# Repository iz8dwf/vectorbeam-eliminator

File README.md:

# vectorbeam-eliminator
Digital to analog vector monitor adapter for B&amp;W Vectorbeam/Cinematronics arcade

This board is described and demonstrated in this video:
https://www.youtube.com/watch?v=j_siDBxwS5w

It allows using an "Atari"-compatible arcade analog vector monitor with a CCPU arcade logic board.

It is highly recommended that the circuit initial check is done using an oscilloscope in X-Y mode first,
at least for the offset tuning.

A misbehaving CCPU board can output bad vector data that can damage the vector monitor (and its own digital monitor too)!
Make sure the logic board at least is executing correctly or use an oscilloscope as XY display to stay on the safe side.

USE AT YOUR OWN RISK!

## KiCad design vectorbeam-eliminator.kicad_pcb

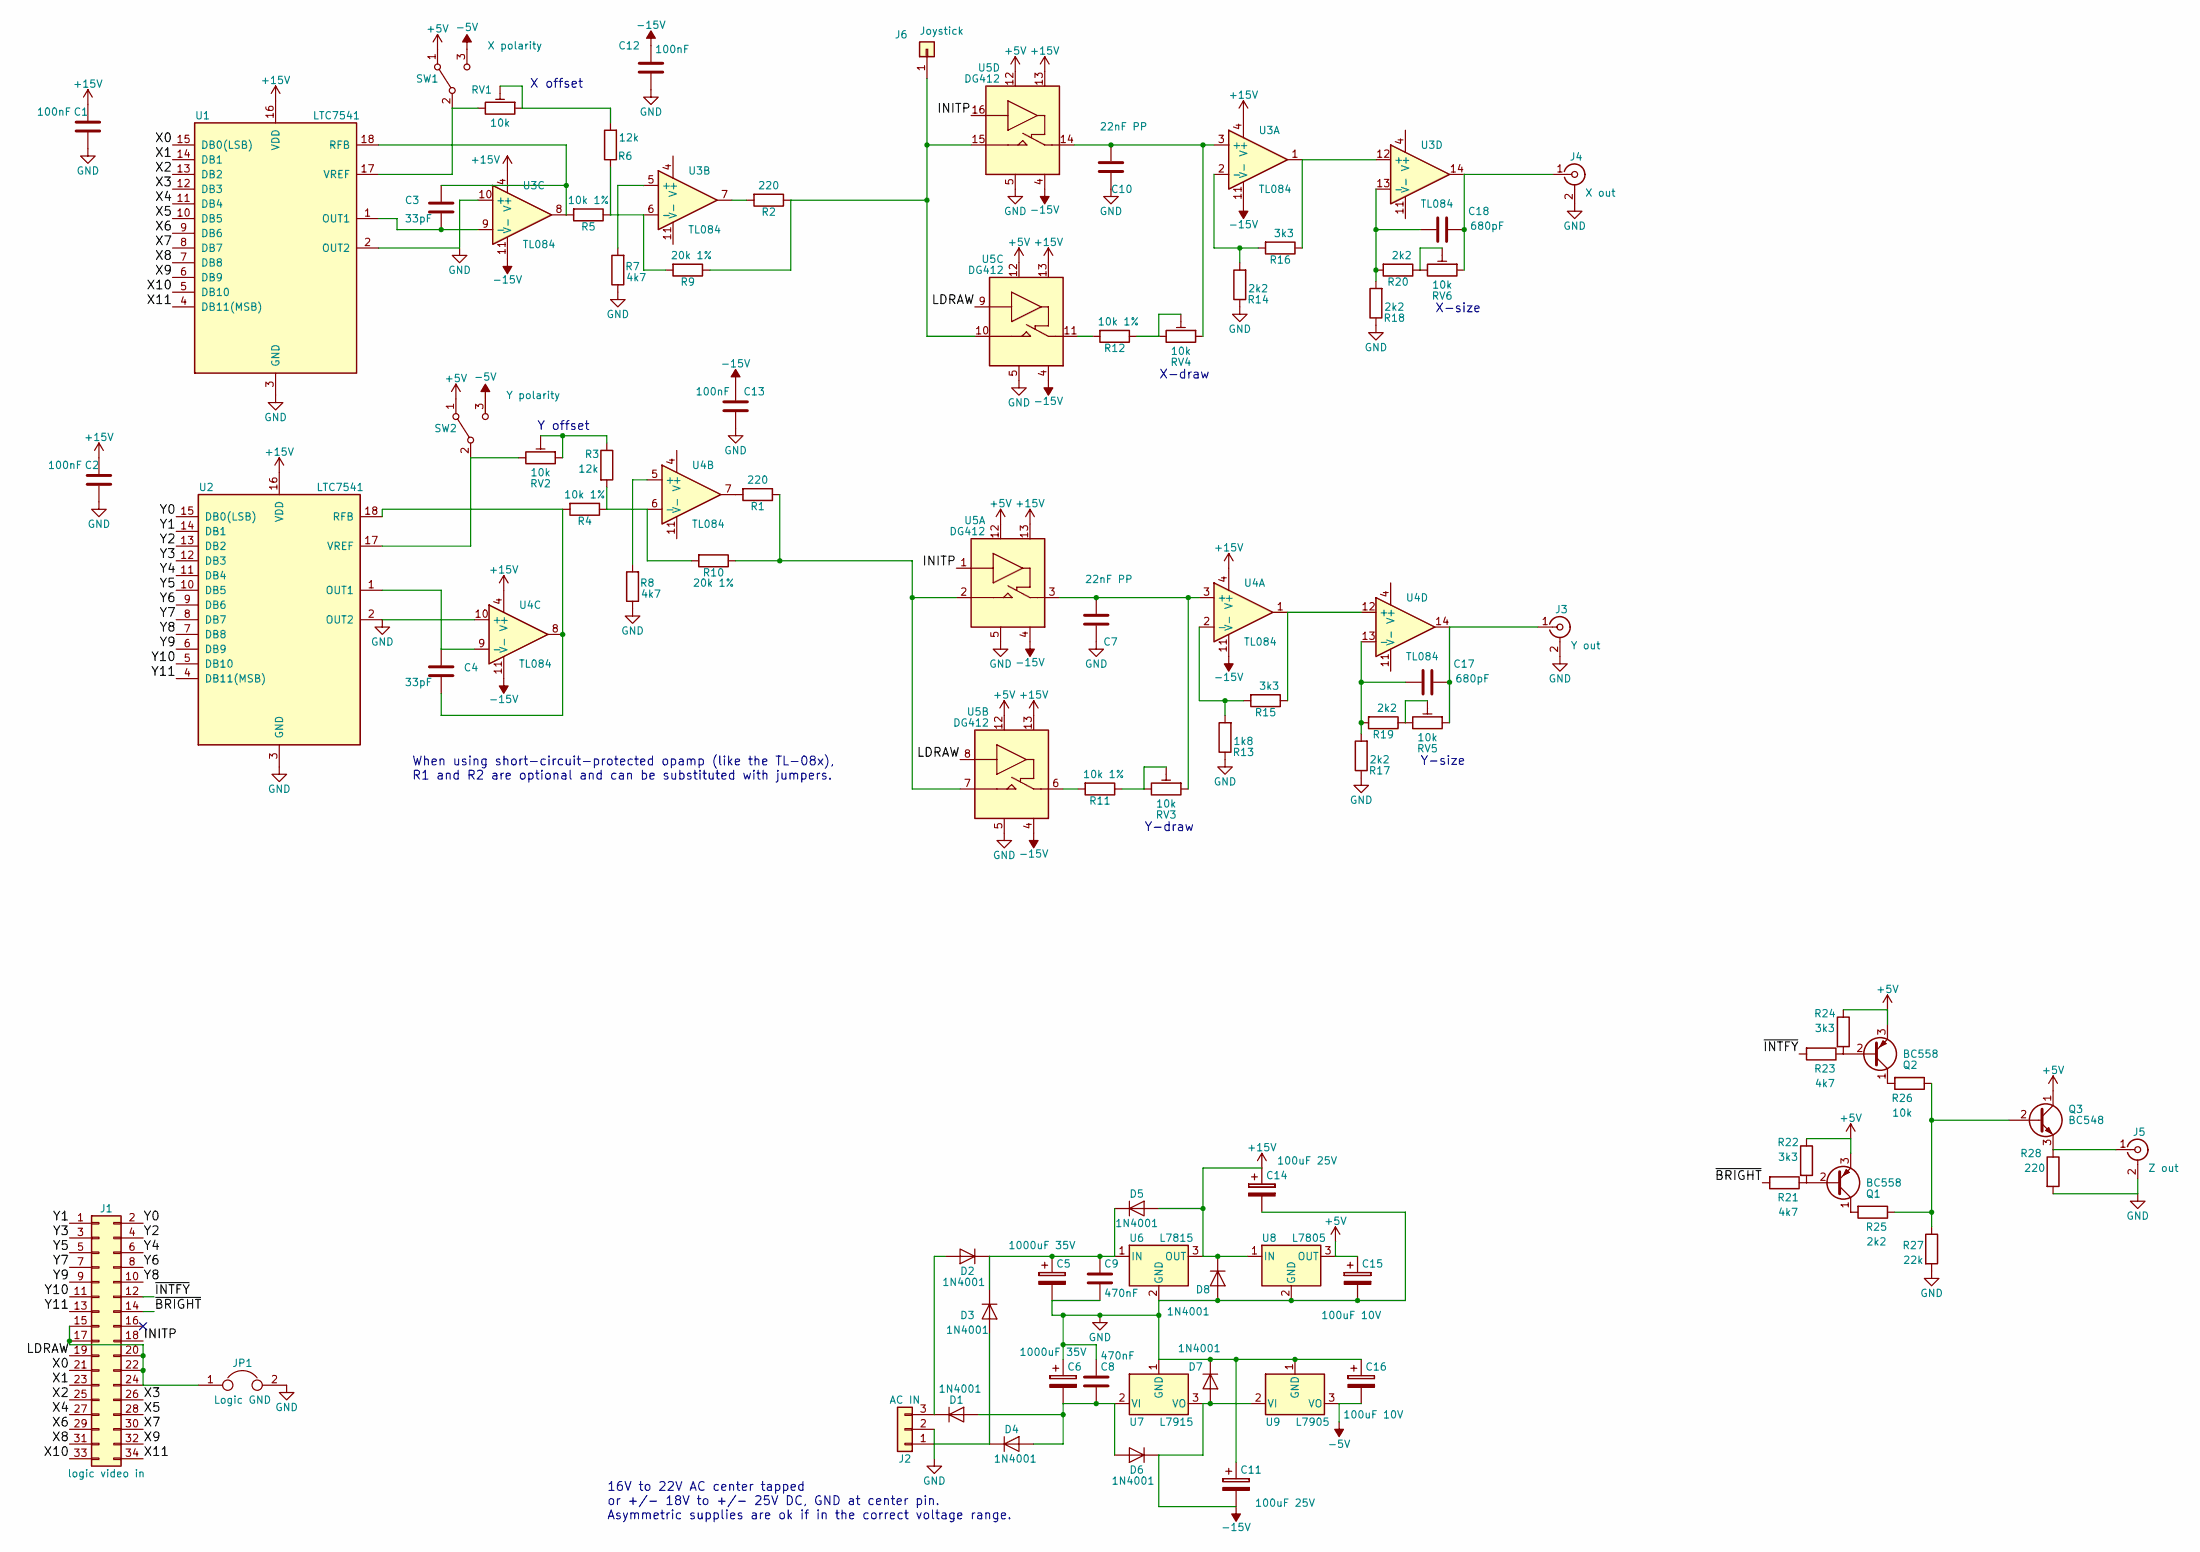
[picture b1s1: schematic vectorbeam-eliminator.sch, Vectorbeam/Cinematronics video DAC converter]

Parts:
C1, C2, C12, C13: 100nF; C_Rect_L7.2mm_W5.5mm_P5.00mm_FKS2_FKP2_MKS2_MKP2
C3, C4: 33pF; C_Disc_D3.8mm_W2.6mm_P2.50mm
C5, C6: 1000uF 35V; CP_Radial_D12.5mm_P5.00mm
C7, C10: 22nF PP; C_Rect_L7.2mm_W7.2mm_P5.00mm_FKS2_FKP2_MKS2_MKP2
C8, C9: 470nF; C_Rect_L7.2mm_W5.5mm_P5.00mm_FKS2_FKP2_MKS2_MKP2
C11, C14: 100uF 25V; CP_Radial_D8.0mm_P2.50mm
C15, C16: 100uF 10V; CP_Radial_D8.0mm_P2.50mm
C17, C18: 680pF; C_Disc_D3.8mm_W2.6mm_P2.50mm
D1, D2, D3, D4, D5, D6, D7, D8: 1N4001; D_DO-41_SOD81_P10.16mm_Horizontal
J1: logic video in; IDC-Header_2x17_Pitch2.54mm_Straight
J2: AC IN; PINHEAD1-3
J3: Y out; phono_single_angled
J4: X out; phono_single_angled
J5: Z out; phono_single_angled
J6: Joystick; Test_Point_Loop_D2.50mm_Drill1.0mm
JP1: Logic GND; PINHEAD1-2
Q1, Q2: BC558; TO-92_Molded_Narrow
Q3: BC548; TO-92_Molded_Narrow
R1, R2, R28: 220; R_1206_HandSoldering
R3, R6: 12k; R_1206_HandSoldering
R4, R5, R11, R12: 10k 1%; R_1206_HandSoldering
R7, R8, R21, R23: 4k7; R_1206_HandSoldering
R9, R10: 20k 1%; R_1206_HandSoldering
R13: 1k8; R_1206_HandSoldering
R14, R17, R18, R19, R20, R25: 2k2; R_1206_HandSoldering
R15, R16, R22, R24: 3k3; R_1206_HandSoldering
R26: 10k; R_1206_HandSoldering
R27: 22k; R_1206_HandSoldering
RV1, RV2, RV3, RV4, RV5, RV6: 10k; Potentiometer_Trimmer_ACP_CA9v_Horizontal_Px10.0mm_Py5.0mm
SW1: X polarity; Pin_Header_Straight_1x03_Pitch2.54mm
SW2: Y polarity; Pin_Header_Straight_1x03_Pitch2.54mm
U1, U2: LTC7541; DIP-18_W7.62mm_Socket
U3, U4: TL084; DIP-14_W7.62mm_Socket
U5: DG412; SOIC-16_3.9x9.9mm_Pitch1.27mm
U6: L7815; TO-220-3_Vertical
U7: L7915; TO-220-3_Vertical
U8: L7805; TO-220-3_Vertical
U9: L7905; TO-220-3_Vertical

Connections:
+5V: C15.1, Q1.3 (E), Q2.3 (E), Q3.1 (C), R22.1, R24.1, SW1.1 (A), SW2.1 (A), U5.12 (VCC), U8.3 (OUT)
+15V: C1.1, C2.1, C14.1, D5.2 (A), D8.1 (K), U1.16 (VDD), U2.16 (VDD), U3.4 (V+), U4.4 (V+), U5.13 (V+), U6.3 (OUT), U8.1 (IN)
-5V: C16.2, SW1.3 (C), SW2.3 (C), U9.3 (VO)
-15V: C11.2, C12.1, C13.1, D6.1 (K), D7.2 (A), U3.11 (V-), U4.11 (V-), U5.4 (V-), U7.3 (VO), U9.2 (VI)
/INITP: J1.18, U5.1 (SW), U5.16 (SW)
/LDRAW: J1.19, U5.8 (SW), U5.9 (SW)
/X0: J1.21, U1.15 (DB0(LSB))
/X1: J1.23, U1.14 (DB1)
/X2: J1.25, U1.13 (DB2)
/X3: J1.26, U1.12 (DB3)
/X4: J1.27, U1.11 (DB4)
/X5: J1.28, U1.10 (DB5)
/X6: J1.29, U1.9 (DB6)
/X7: J1.30, U1.8 (DB7)
/X8: J1.31, U1.7 (DB8)
/X9: J1.32, U1.6 (DB9)
/X10: J1.33, U1.5 (DB10)
/X11: J1.34, U1.4 (DB11(MSB))
/Y0: J1.2, U2.15 (DB0(LSB))
/Y1: J1.1, U2.14 (DB1)
/Y2: J1.4, U2.13 (DB2)
/Y3: J1.3, U2.12 (DB3)
/Y4: J1.6, U2.11 (DB4)
/Y5: J1.5, U2.10 (DB5)
/Y6: J1.8, U2.9 (DB6)
/Y7: J1.7, U2.8 (DB7)
/Y8: J1.10, U2.7 (DB8)
/Y9: J1.9, U2.6 (DB9)
/Y10: J1.11, U2.5 (DB10)
/Y11: J1.13, U2.4 (DB11(MSB))
/~BRIGHT: J1.14, R21.2
/~INTFY: J1.12, R23.2
GND: C1.2, C2.2, C5.2, C6.1, C7.1, C8.1, C9.2, C10.1, C11.1, C12.2, C13.2, C14.2, C15.2, C16.1, D7.1 (K), D8.2 (A), J2.2, J3.2 (Ext), J4.2 (Ext), J5.2 (Ext), JP1.2, R7.1, R8.1, R13.1, R14.1, R17.1, R18.1, R27.2, R28.2, U1.2 (OUT2), U1.3 (GND), U2.2 (OUT2), U2.3 (GND), U3.10 (+), U4.10 (+), U5.5 (GND), U6.2 (GND), U7.1 (GND), U8.2 (GND), U9.1 (GND)
unnamed: C3.1, R5.2, U1.18 (RFB), U3.8
unnamed: C3.2, U1.1 (OUT1), U3.9 (-)
unnamed: C4.1, U2.1 (OUT1), U4.9 (-)
unnamed: C4.2, R4.2, U2.18 (RFB), U4.8
unnamed: C5.1, C9.1, D2.1 (K), D3.1 (K), D5.1 (K), U6.1 (IN)
unnamed: C6.2, C8.2, D1.2 (A), D4.2 (A), D6.2 (A), U7.2 (VI)
unnamed 39: C7.2, RV3.1, U4.3 (+), U5.3 (OUT); also elsewhere on the board
unnamed 40: C10.2, RV4.1, U3.3 (+), U5.14 (OUT); also elsewhere on the board
unnamed: C17.1, R17.2, R19.2, U4.13 (-)
unnamed 42: C17.2, J3.1 (In), RV5.1, U4.14; also elsewhere on the board
unnamed: C18.1, R18.2, R20.2, U3.13 (-)
unnamed 44: C18.2, J4.1 (In), RV6.1, U3.14; also elsewhere on the board
unnamed: D1.1 (K), D2.2 (A), J2.3
unnamed: D3.2 (A), D4.1 (K), J2.1
unnamed: J1.15, J1.17, J1.20, J1.22, J1.24, JP1.1
unnamed: J5.1 (In), Q3.3 (E), R28.1
unnamed: J6.1, R2.1, R9.1, U5.10 (IN), U5.15 (IN)
unnamed: Q1.1 (C), R25.2
unnamed: Q1.2 (B), R21.1, R22.2
unnamed: Q2.1 (C), R26.2
unnamed: Q2.2 (B), R23.1, R24.2
unnamed: Q3.2 (B), R25.1, R26.1, R27.1
unnamed: R1.1, R10.1, U5.2 (IN), U5.7 (IN)
unnamed: R1.2, U4.7
unnamed: R2.2, U3.7
unnamed 59: R3.1, RV2.1, RV2.2; also elsewhere on the board
unnamed: R5.1, R6.1, R9.2, U3.6 (-)
unnamed 61: R6.2, RV1.1, RV1.2; also elsewhere on the board
unnamed: R7.2, U3.5 (+)
unnamed: R8.2, U4.5 (+)
unnamed: R3.2, R4.1, R10.2, U4.6 (-)
unnamed 65: R11.1, RV3.2, RV3.3; also elsewhere on the board
unnamed: R11.2, U5.6 (OUT)
unnamed 67: R12.1, RV4.2, RV4.3; also elsewhere on the board
unnamed: R12.2, U5.11 (OUT)
unnamed: R13.2, R15.2, U4.2 (-)
unnamed: R14.2, R16.2, U3.2 (-)
unnamed: R15.1, U4.1, U4.12 (+)
unnamed: R16.1, U3.1, U3.12 (+)
unnamed 73: R19.1, RV5.2, RV5.3; also elsewhere on the board
unnamed 74: R20.1, RV6.2, RV6.3; also elsewhere on the board
unnamed 75: RV1.3, SW1.2 (B), U1.17 (VREF); also elsewhere on the board
unnamed 76: RV2.3, SW2.2 (B), U2.17 (VREF); also elsewhere on the board

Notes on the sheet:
X-draw
X-size
Y-draw
Y-size
X offset
Y offset
When using short-circuit-protected opamp (like the TL-08x), R1 and R2 are optional and can be substituted with jumpers.
16V to 22V AC center tapped or +/- 18V to +/- 25V DC, GND at center pin. Asymmetric supplies are ok if in the correct voltage range.

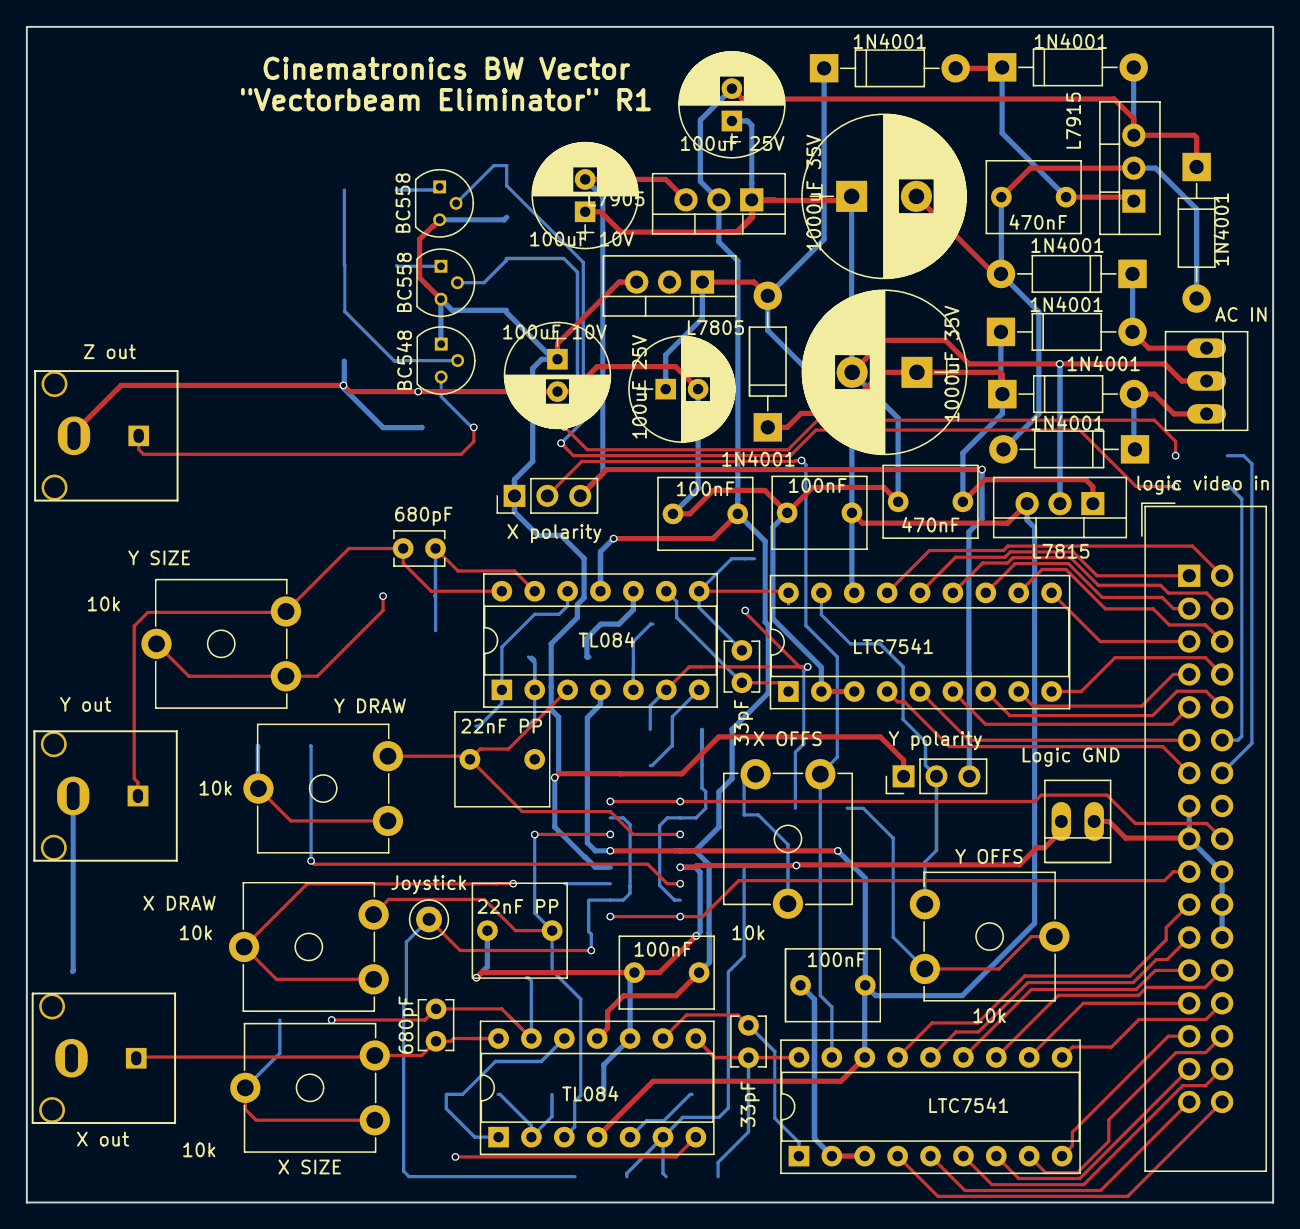
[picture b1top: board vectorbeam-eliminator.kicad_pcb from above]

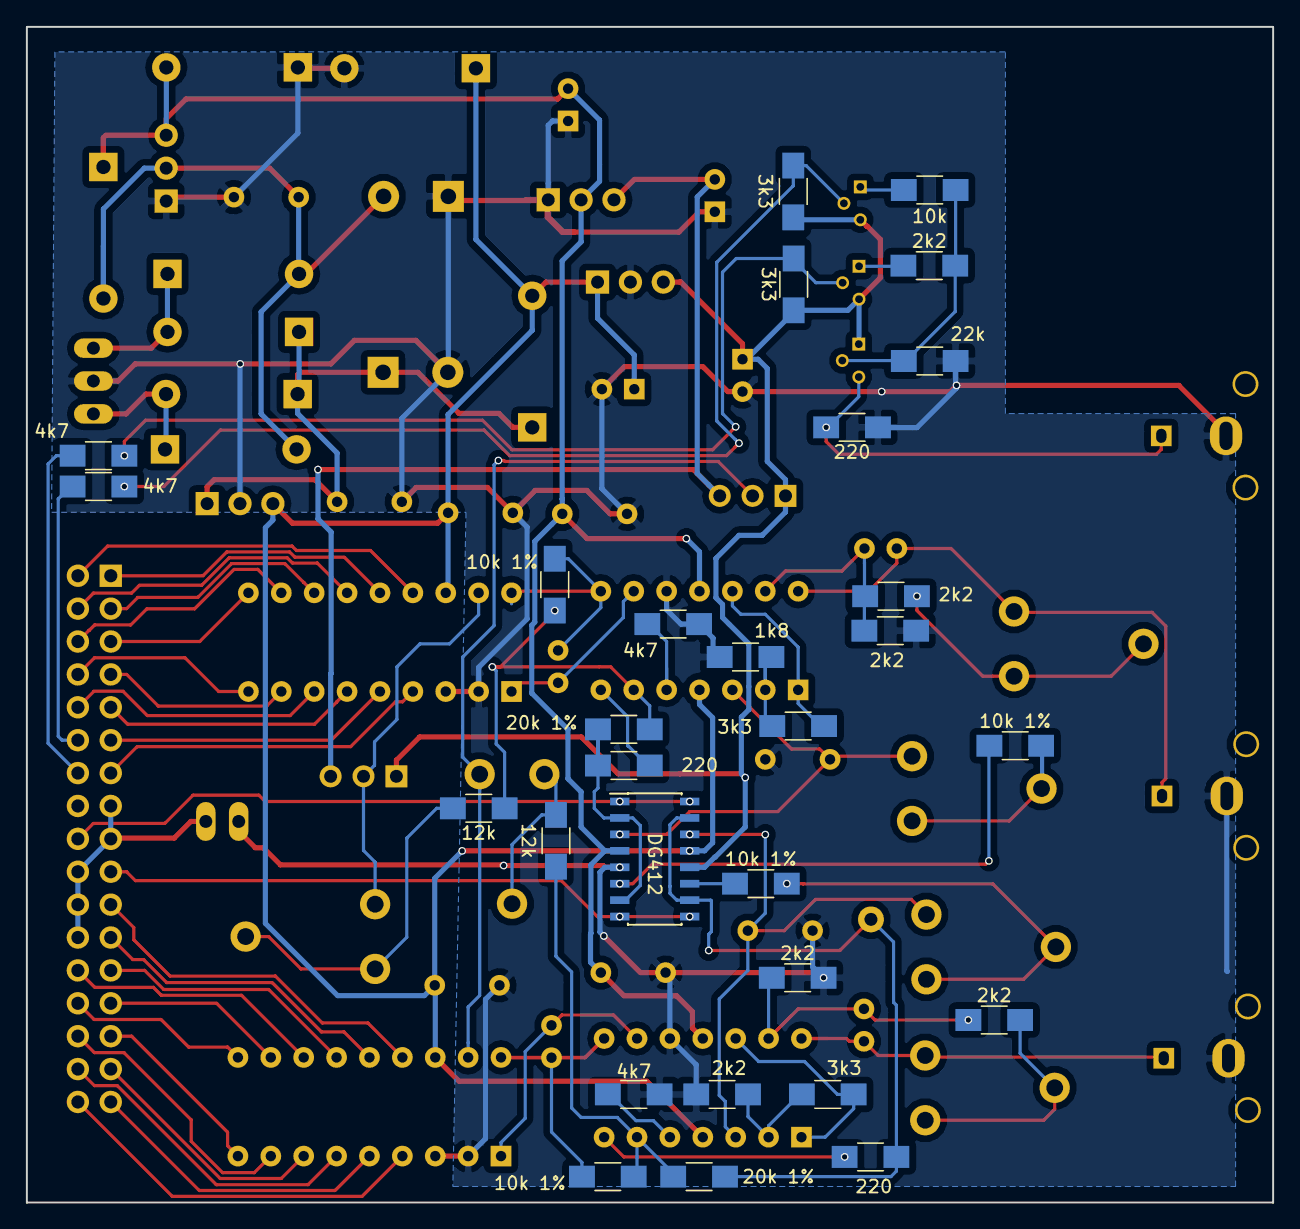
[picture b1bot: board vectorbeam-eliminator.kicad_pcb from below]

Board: 2 copper layers, 96.2 x 90.8 mm, 81 parts (29 on the bottom side), 76 nets.

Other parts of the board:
X DRAW: 10k; Potentiometer_Trimmer_ACP_CA9v_Horizontal_Px10.0mm_Py5.0mm
X OFFS: 10k; Potentiometer_Trimmer_ACP_CA9v_Horizontal_Px10.0mm_Py5.0mm
X SIZE: 10k; Potentiometer_Trimmer_ACP_CA9v_Horizontal_Px10.0mm_Py5.0mm
Y DRAW: 10k; Potentiometer_Trimmer_ACP_CA9v_Horizontal_Px10.0mm_Py5.0mm
Y OFFS: 10k; Potentiometer_Trimmer_ACP_CA9v_Horizontal_Px10.0mm_Py5.0mm
Y SIZE: 10k; Potentiometer_Trimmer_ACP_CA9v_Horizontal_Px10.0mm_Py5.0mm

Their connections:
unnamed 39: Y DRAW.1; also elsewhere on the board
unnamed 40: X DRAW.1; also elsewhere on the board
unnamed 42: Y SIZE.1; also elsewhere on the board
unnamed 44: X SIZE.1; also elsewhere on the board
unnamed 59: Y OFFS.1, Y OFFS.2; also elsewhere on the board
unnamed 61: X OFFS.1, X OFFS.2; also elsewhere on the board
unnamed 65: Y DRAW.2, Y DRAW.3; also elsewhere on the board
unnamed 67: X DRAW.2, X DRAW.3; also elsewhere on the board
unnamed 73: Y SIZE.2, Y SIZE.3; also elsewhere on the board
unnamed 74: X SIZE.2, X SIZE.3; also elsewhere on the board
unnamed 75: X OFFS.3; also elsewhere on the board
unnamed 76: Y OFFS.3; also elsewhere on the board

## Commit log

2023-12-15 initial release
